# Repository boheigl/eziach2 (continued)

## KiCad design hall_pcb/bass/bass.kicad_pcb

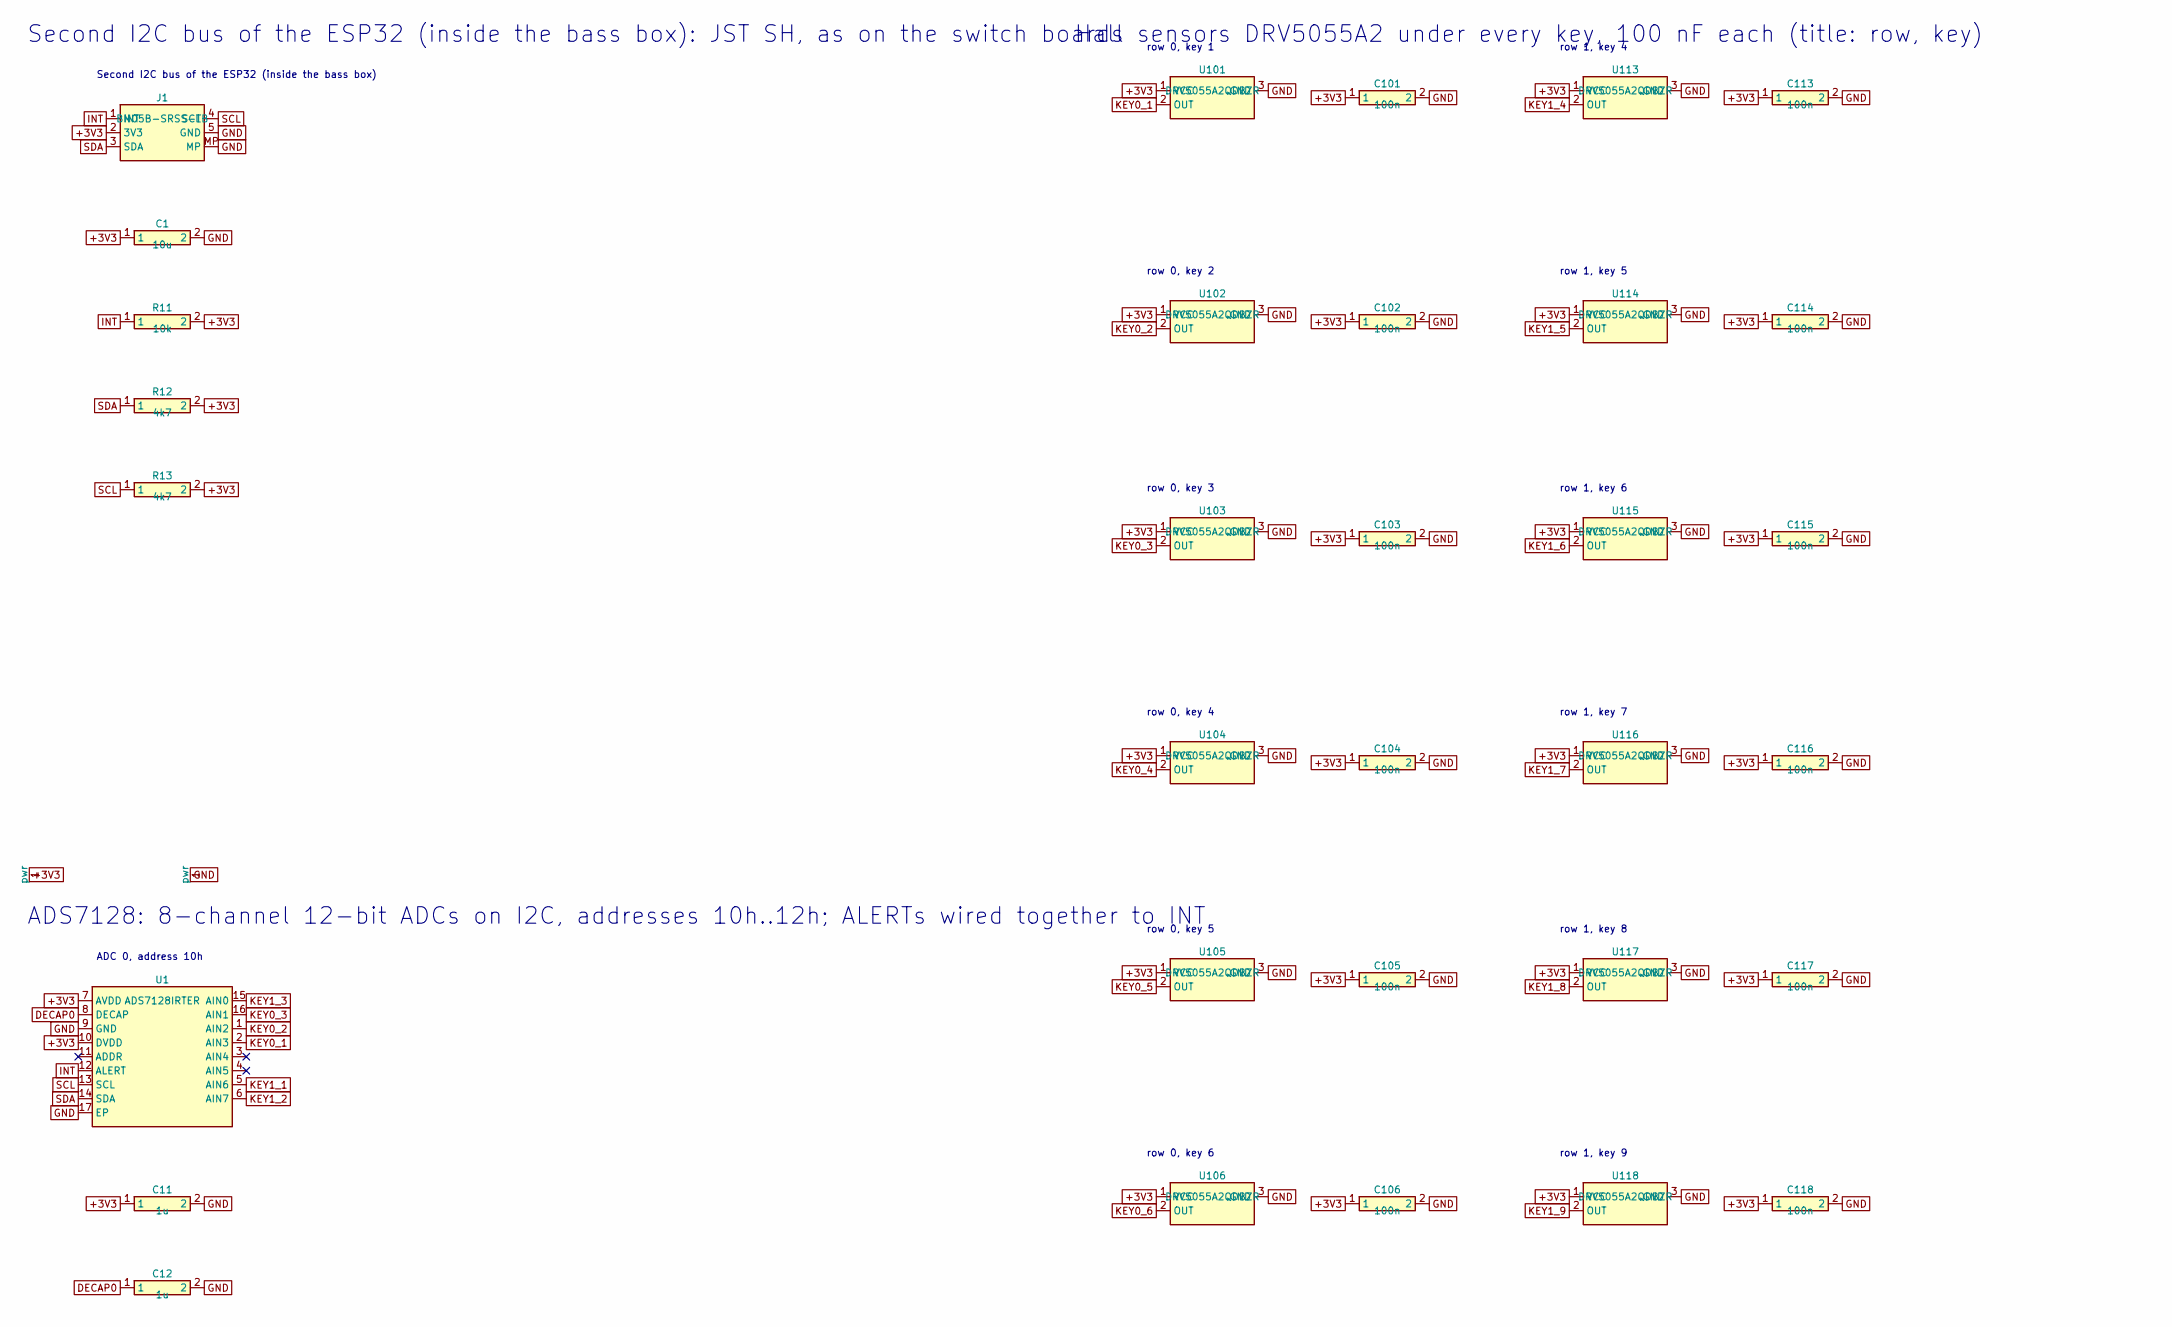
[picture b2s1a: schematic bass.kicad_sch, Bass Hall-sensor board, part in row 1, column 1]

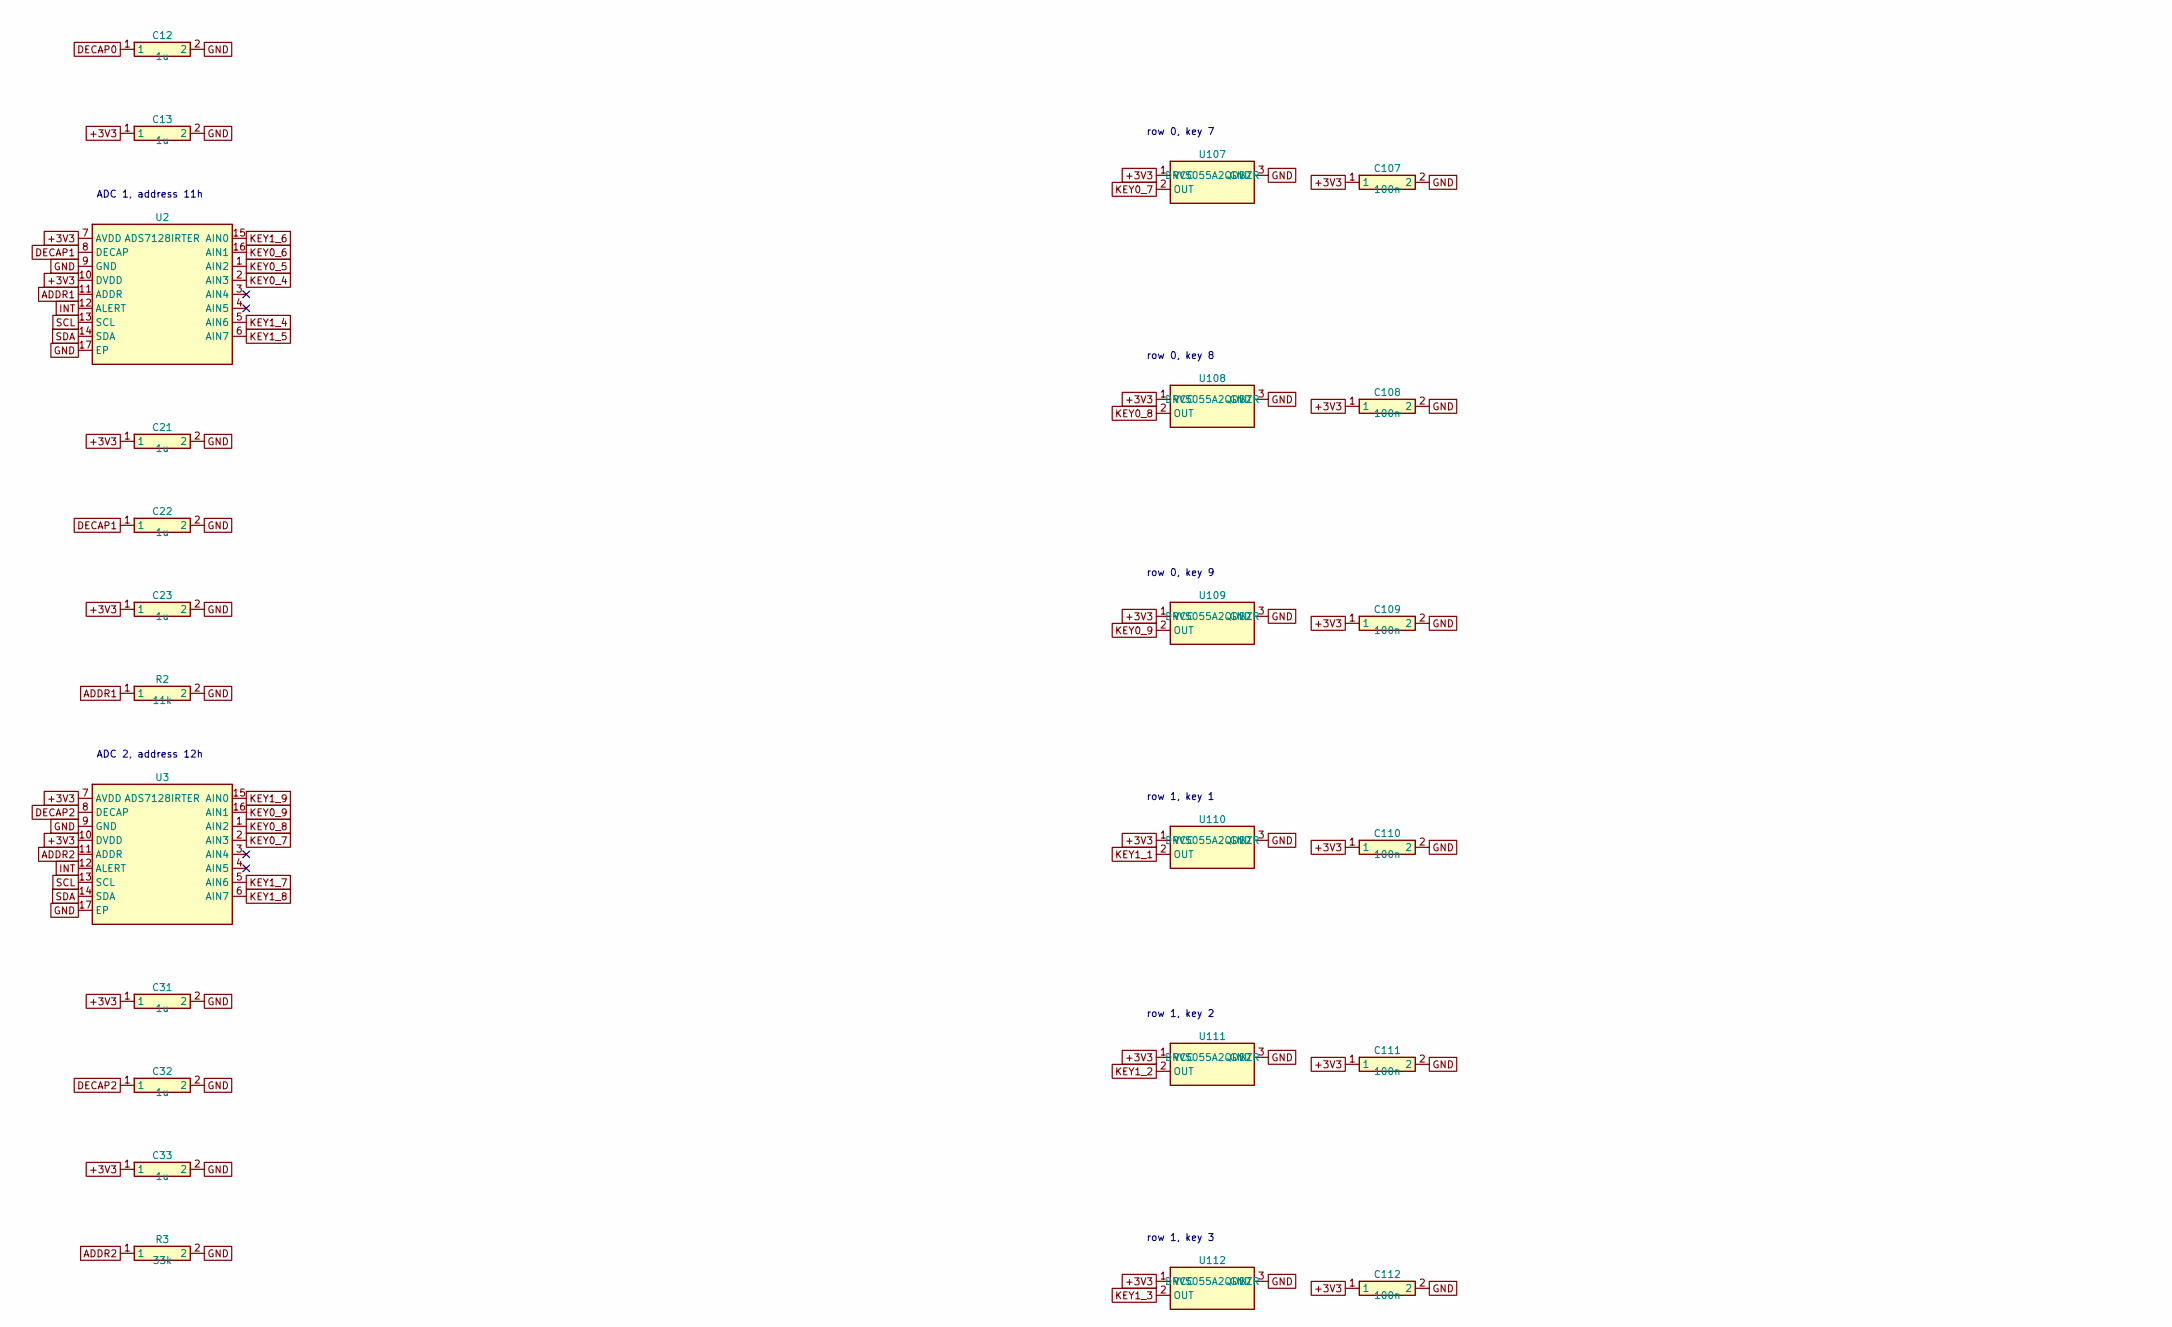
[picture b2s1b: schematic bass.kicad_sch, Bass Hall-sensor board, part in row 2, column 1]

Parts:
C1: 10u; C_0805_2012Metric; LCSC C15850
C11, C12, C13, C21, C22, C23, C31, C32, C33: 1u; C_0402_1005Metric; LCSC C52923
C101, C102, C103, C104, C105, C106, C107, C108, C109, C110, C111, C112, C113, C114, C115, C116, C117, C118: 100n; C_0402_1005Metric; LCSC C1525
J1: BM05B-SRSS-TB; JST_SH_BM05B-SRSS-TB_1x05-1MP_P1.00mm_Vertical; LCSC C160391
R2: 11k; R_0402_1005Metric; LCSC C25749
R3: 33k; R_0402_1005Metric; LCSC C25779
R11: 10k; R_0402_1005Metric; LCSC C25744
R12, R13: 4k7; R_0402_1005Metric; LCSC C25900
U1, U2, U3: ADS7128IRTER; WQFN-16-1EP_3x3mm_P0.5mm_EP1.68x1.68mm; LCSC C2867992
U101, U102, U103, U104, U105, U106, U107, U108, U109, U110, U111, U112, U113, U114, U115, U116, U117, U118: DRV5055A2QDBZR; SOT-23; LCSC C266131

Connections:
+3V3: C1.1, C11.1, C13.1, C21.1, C23.1, C31.1, C33.1, C101.1, C102.1, C103.1, C104.1, C105.1, C106.1, C107.1, C108.1, C109.1, C110.1, C111.1, C112.1, C113.1, C114.1, C115.1, C116.1, C117.1, C118.1, J1.2 (3V3), R11.2, R12.2, R13.2, U1.7 (AVDD), U1.10 (DVDD), U2.7 (AVDD), U2.10 (DVDD), U3.7 (AVDD), U3.10 (DVDD), U101.1 (VCC), U102.1 (VCC), U103.1 (VCC), U104.1 (VCC), U105.1 (VCC), U106.1 (VCC), U107.1 (VCC), U108.1 (VCC), U109.1 (VCC), U110.1 (VCC), U111.1 (VCC), U112.1 (VCC), U113.1 (VCC), U114.1 (VCC), U115.1 (VCC), U116.1 (VCC), U117.1 (VCC), U118.1 (VCC)
ADDR1: R2.1, U2.11 (ADDR)
ADDR2: R3.1, U3.11 (ADDR)
DECAP0: C12.1, U1.8 (DECAP)
DECAP1: C22.1, U2.8 (DECAP)
DECAP2: C32.1, U3.8 (DECAP)
GND: C1.2, C11.2, C12.2, C13.2, C21.2, C22.2, C23.2, C31.2, C32.2, C33.2, C101.2, C102.2, C103.2, C104.2, C105.2, C106.2, C107.2, C108.2, C109.2, C110.2, C111.2, C112.2, C113.2, C114.2, C115.2, C116.2, C117.2, C118.2, J1.5 (GND), J1.MP, R2.2, R3.2, U1.9 (GND), U1.17 (EP), U2.9 (GND), U2.17 (EP), U3.9 (GND), U3.17 (EP), U101.3 (GND), U102.3 (GND), U103.3 (GND), U104.3 (GND), U105.3 (GND), U106.3 (GND), U107.3 (GND), U108.3 (GND), U109.3 (GND), U110.3 (GND), U111.3 (GND), U112.3 (GND), U113.3 (GND), U114.3 (GND), U115.3 (GND), U116.3 (GND), U117.3 (GND), U118.3 (GND)
INT: J1.1 (INT), R11.1, U1.12 (ALERT), U2.12 (ALERT), U3.12 (ALERT)
KEY0_1: U1.2 (AIN3), U101.2 (OUT)
KEY0_2: U1.1 (AIN2), U102.2 (OUT)
KEY0_3: U1.16 (AIN1), U103.2 (OUT)
KEY0_4: U2.2 (AIN3), U104.2 (OUT)
KEY0_5: U2.1 (AIN2), U105.2 (OUT)
KEY0_6: U2.16 (AIN1), U106.2 (OUT)
KEY0_7: U3.2 (AIN3), U107.2 (OUT)
KEY0_8: U3.1 (AIN2), U108.2 (OUT)
KEY0_9: U3.16 (AIN1), U109.2 (OUT)
KEY1_1: U1.5 (AIN6), U110.2 (OUT)
KEY1_2: U1.6 (AIN7), U111.2 (OUT)
KEY1_3: U1.15 (AIN0), U112.2 (OUT)
KEY1_4: U2.5 (AIN6), U113.2 (OUT)
KEY1_5: U2.6 (AIN7), U114.2 (OUT)
KEY1_6: U2.15 (AIN0), U115.2 (OUT)
KEY1_7: U3.5 (AIN6), U116.2 (OUT)
KEY1_8: U3.6 (AIN7), U117.2 (OUT)
KEY1_9: U3.15 (AIN0), U118.2 (OUT)
SCL: J1.4 (SCL), R13.1, U1.13 (SCL), U2.13 (SCL), U3.13 (SCL)
SDA: J1.3 (SDA), R12.1, U1.14 (SDA), U2.14 (SDA), U3.14 (SDA)

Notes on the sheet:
Second I2C bus of the ESP32 (inside the bass box): JST SH, as on the switch boards
Second I2C bus of the ESP32 (inside the bass box)
ADS7128: 8-channel 12-bit ADCs on I2C, addresses 10h..12h; ALERTs wired together to INT
ADC 0, address 10h
ADC 1, address 11h
ADC 2, address 12h
Hall sensors DRV5055A2 under every key, 100 nF each (title: row, key)
row 0, key 1
row 0, key 2
row 0, key 3
row 0, key 4
row 0, key 5
row 0, key 6
row 0, key 7
row 0, key 8
row 0, key 9
row 1, key 1
row 1, key 2
row 1, key 3
row 1, key 4
row 1, key 5
row 1, key 6
row 1, key 7
row 1, key 8
row 1, key 9

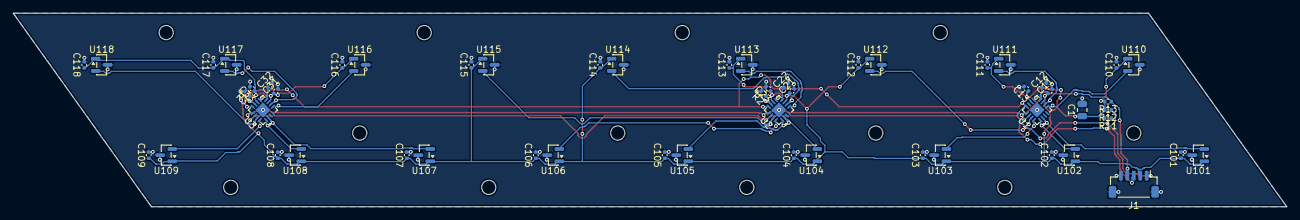
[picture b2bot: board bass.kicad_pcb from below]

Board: 2 copper layers, 197.4 x 30.0 mm, 55 parts (55 on the bottom side), 28 nets.

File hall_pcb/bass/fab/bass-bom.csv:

"Comment","Designator","Footprint","LCSC","Quantity"
"10u","C1","Capacitor_SMD:C_0805_2012Metric","C15850","1"
"100n","C101,C102,C103,C104,C105,C106,C107,C108,C109,C110,C111,C112,C113,C114,C115,C116,C117,C118","Capacitor_SMD:C_0402_1005Metric","C1525","18"
"1u","C11,C12,C13,C21,C22,C23,C31,C32,C33","Capacitor_SMD:C_0402_1005Metric","C52923","9"
"BM05B-SRSS-TB","J1","Connector_JST:JST_SH_BM05B-SRSS-TB_1x05-1MP_P1.00mm_Vertical","C160391","1"
"11k","R2","Resistor_SMD:R_0402_1005Metric","C25749","1"
"33k","R3","Resistor_SMD:R_0402_1005Metric","C25779","1"
"10k","R11","Resistor_SMD:R_0402_1005Metric","C25744","1"
"4k7","R12,R13","Resistor_SMD:R_0402_1005Metric","C25900","2"
"ADS7128IRTER","U1,U2,U3","Package_DFN_QFN:WQFN-16-1EP_3x3mm_P0.5mm_EP1.68x1.68mm","C2867992","3"
"DRV5055A2QDBZR","U101,U102,U103,U104,U105,U106,U107,U108,U109,U110,U111,U112,U113,U114,U115,U116,U117,U118","Package_TO_SOT_SMD:SOT-23","C266131","18"

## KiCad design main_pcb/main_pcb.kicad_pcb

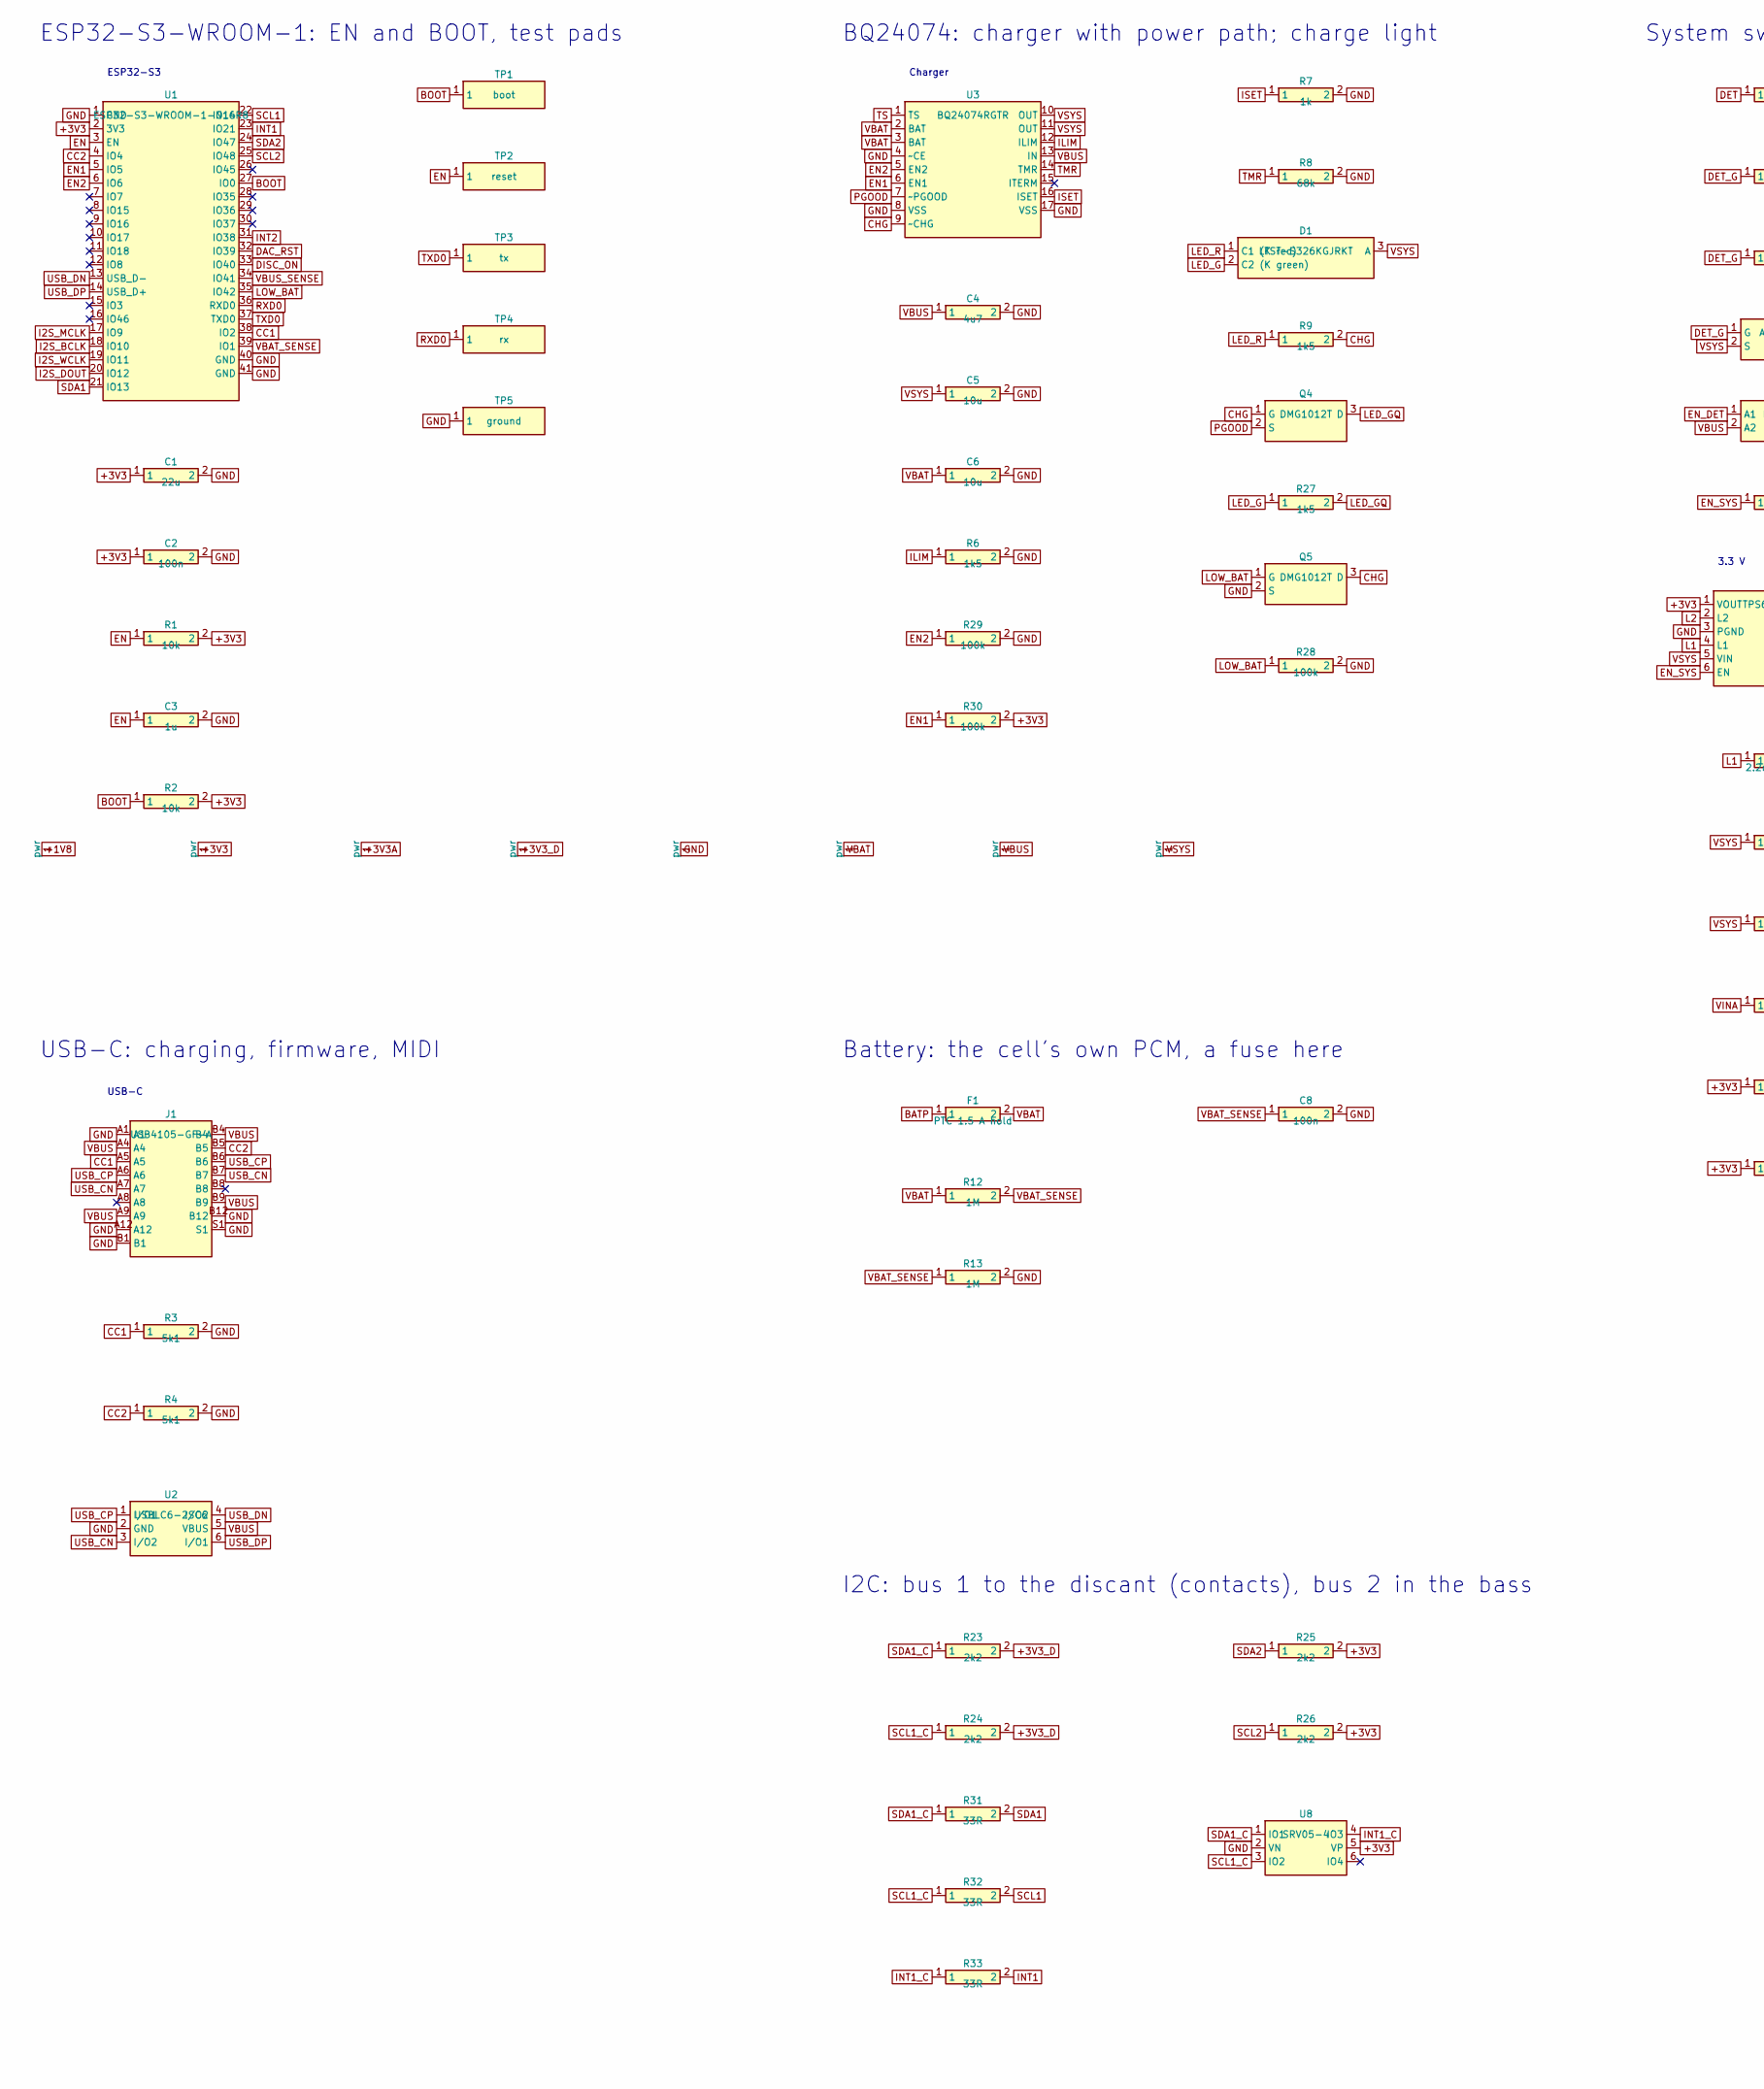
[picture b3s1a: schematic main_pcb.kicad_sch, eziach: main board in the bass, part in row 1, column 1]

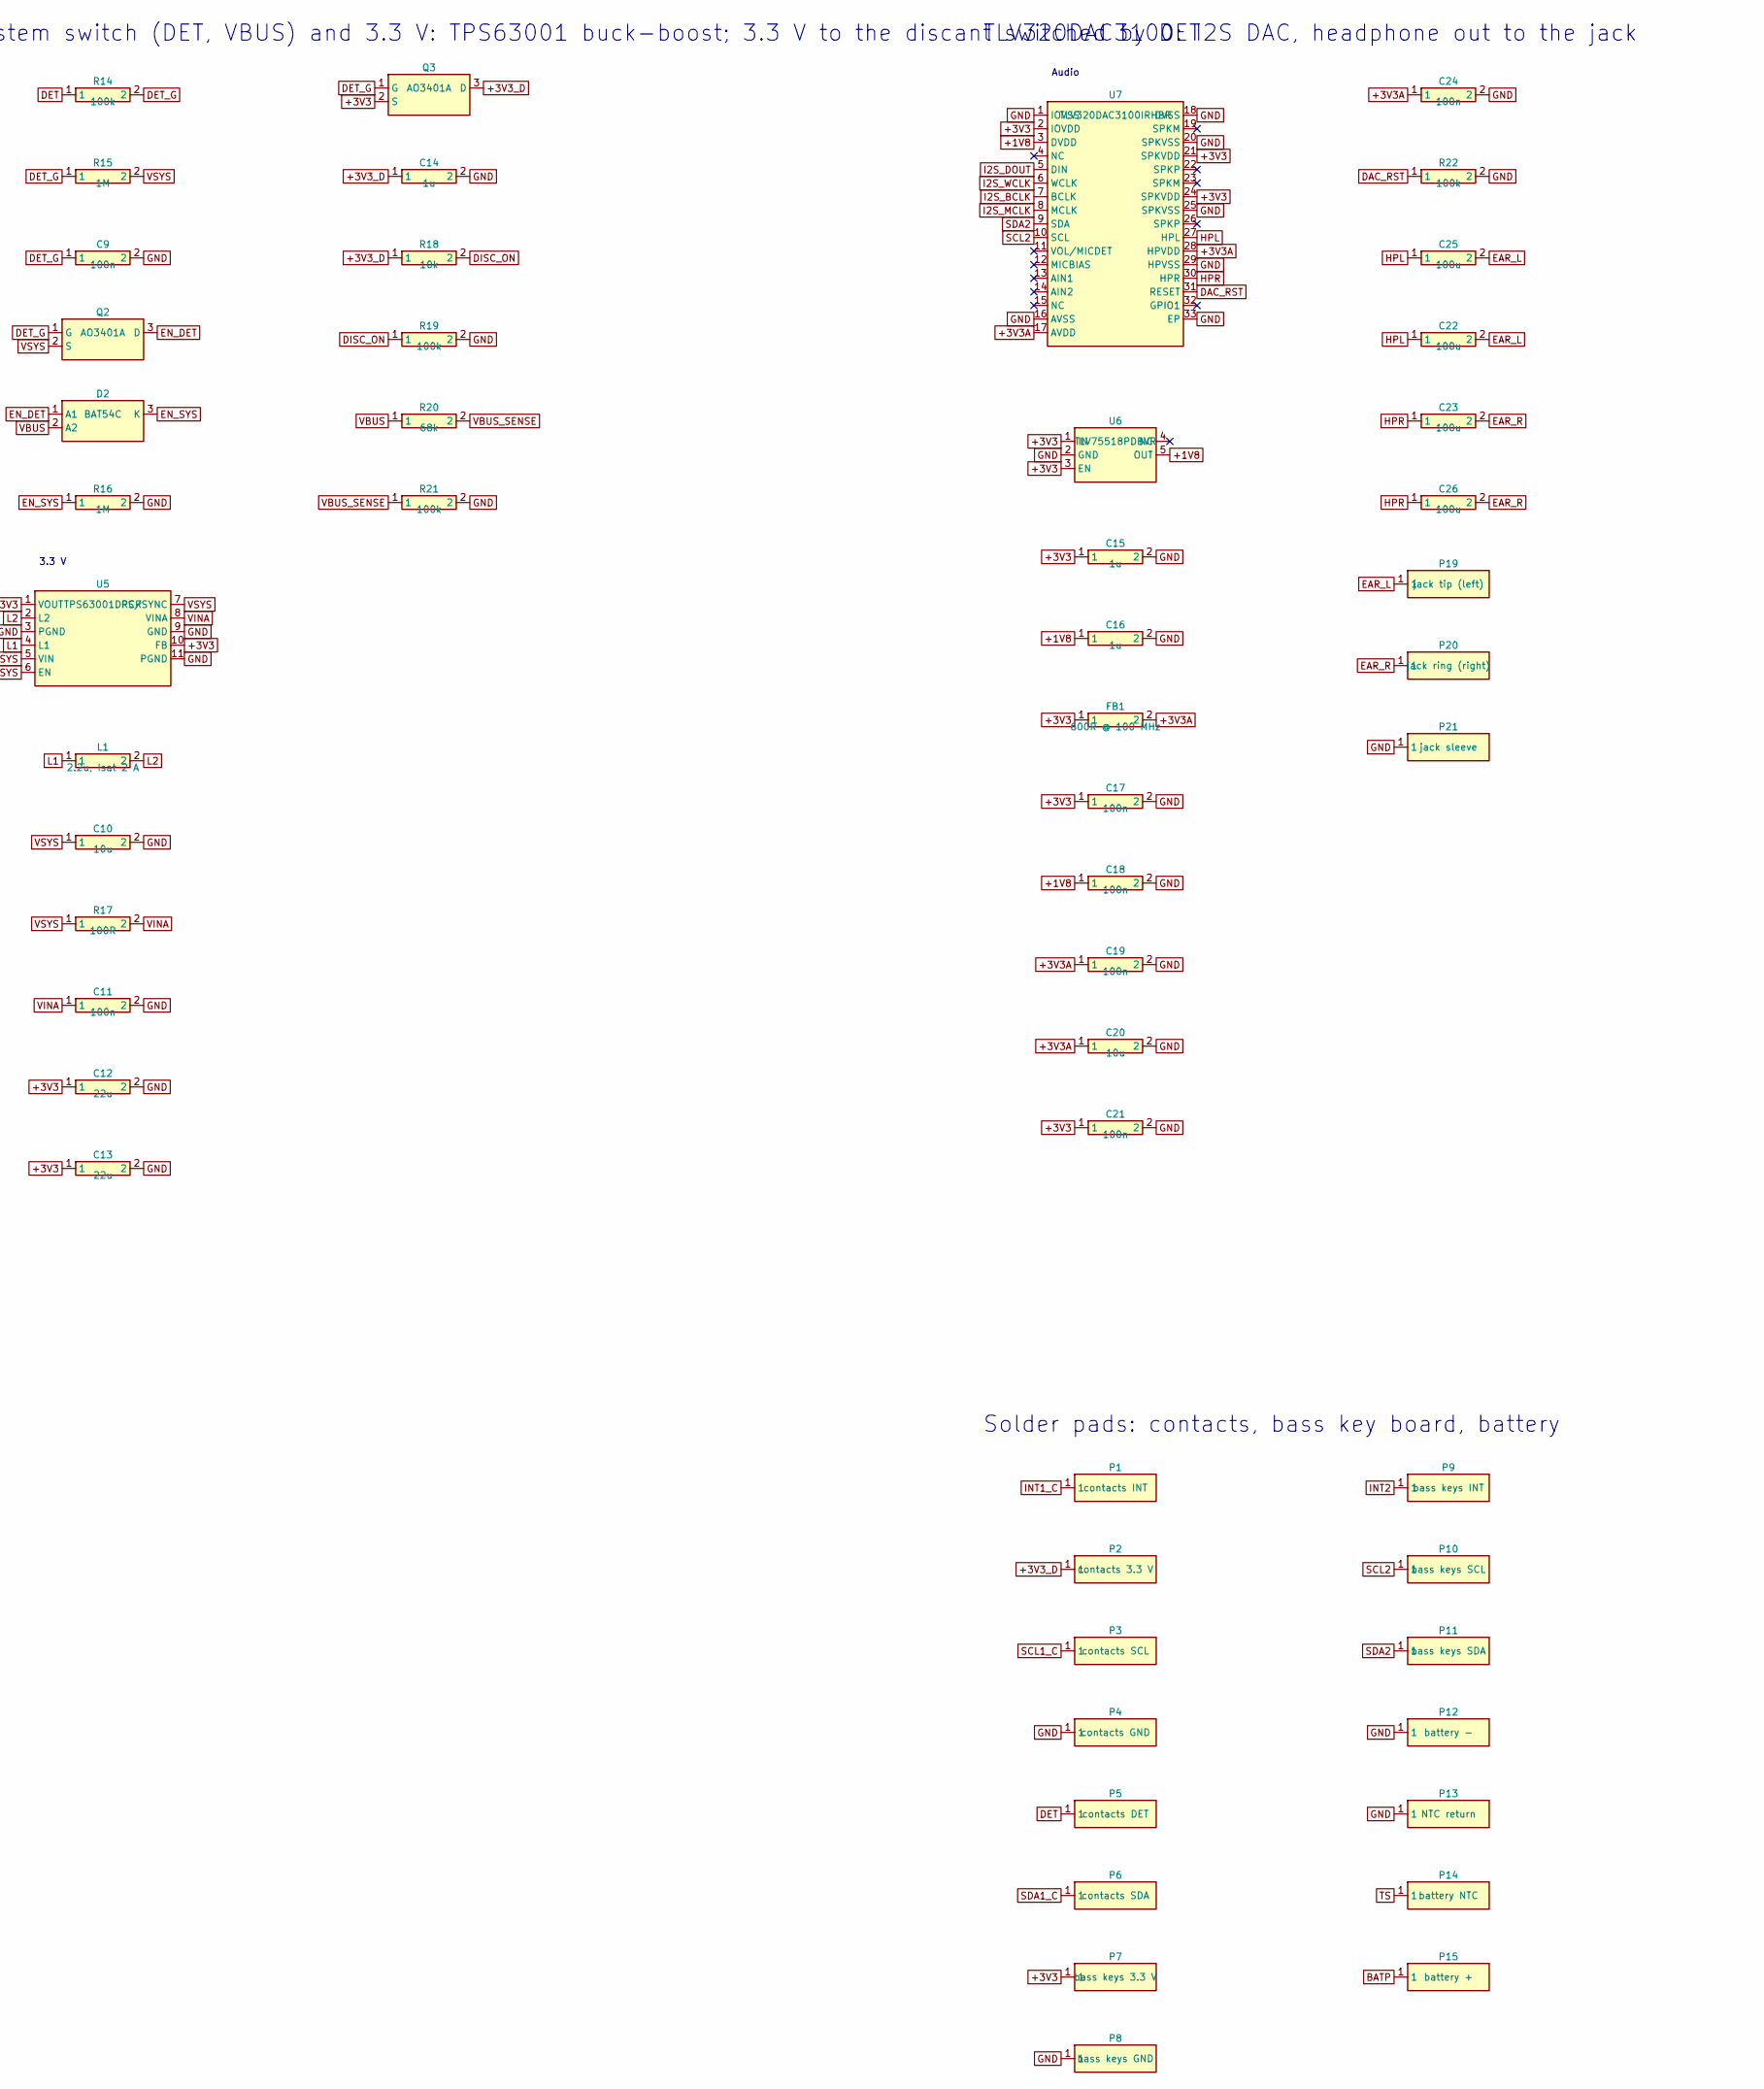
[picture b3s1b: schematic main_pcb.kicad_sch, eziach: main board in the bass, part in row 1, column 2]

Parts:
C1, C12, C13: 22u; C_0805_2012Metric; LCSC C45783
C2, C8, C9, C11, C17, C18, C19, C21, C24: 100n; C_0402_1005Metric; LCSC C1525
C3, C14, C15, C16: 1u; C_0402_1005Metric; LCSC C52923
C4: 4u7; C_0603_1608Metric; LCSC C19666
C5, C6: 10u; C_0603_1608Metric; LCSC C19702
C10: 10u; C_0805_2012Metric; LCSC C15850
C20: 10u; C_0402_1005Metric; LCSC C15525
C22, C23, C25, C26: 100u; C_0805_2012Metric; LCSC C141660
D1: LTST-S326KGJRKT; LED_LiteOn_LTST-S326; LCSC C125116
D2: BAT54C; SOT-23; LCSC C37704
F1: PTC 1.5 A hold; Fuse_1206_3216Metric; LCSC C20802
FB1: 600R @ 100 MHz; L_0402_1005Metric; LCSC C76884
J1: USB4105-GF-A; USB_C_Receptacle_GCT_USB4105-xx-A_16P_TopMnt_Horizontal; LCSC C3020560
L1: 2.2u, Isat 2 A; L_1008_2520Metric; LCSC C23894
P1: contacts INT; TestPoint_THTPad_D1.5mm_Drill0.7mm
P2: contacts 3.3 V; TestPoint_THTPad_D1.5mm_Drill0.7mm
P3: contacts SCL; TestPoint_THTPad_D1.5mm_Drill0.7mm
P4: contacts GND; TestPoint_THTPad_D1.5mm_Drill0.7mm
P5: contacts DET; TestPoint_THTPad_D1.5mm_Drill0.7mm
P6: contacts SDA; TestPoint_THTPad_D1.5mm_Drill0.7mm
P7: bass keys 3.3 V; TestPoint_THTPad_D1.5mm_Drill0.7mm
P8: bass keys GND; TestPoint_THTPad_D1.5mm_Drill0.7mm
P9: bass keys INT; TestPoint_THTPad_D1.5mm_Drill0.7mm
P10: bass keys SCL; TestPoint_THTPad_D1.5mm_Drill0.7mm
P11: bass keys SDA; TestPoint_THTPad_D1.5mm_Drill0.7mm
P12: battery -; TestPoint_THTPad_D1.5mm_Drill0.7mm
P13: NTC return; TestPoint_THTPad_D1.5mm_Drill0.7mm
P14: battery NTC; TestPoint_THTPad_D1.5mm_Drill0.7mm
P15: battery +; TestPoint_THTPad_D1.5mm_Drill0.7mm
P19: jack tip (left); TestPoint_Pad_1.0x1.0mm
P20: jack ring (right); TestPoint_Pad_1.0x1.0mm
P21: jack sleeve; TestPoint_Pad_1.0x1.0mm
Q2, Q3: AO3401A; SOT-23; LCSC C15127
Q4, Q5: DMG1012T; SOT-523; LCSC C20512
R1, R2, R18: 10k; R_0402_1005Metric; LCSC C25744
R3, R4: 5k1; R_0402_1005Metric; LCSC C25905
R6, R9, R27: 1k5; R_0402_1005Metric; LCSC C25867
R7: 1k; R_0402_1005Metric; LCSC C11702
R8, R20: 68k; R_0402_1005Metric; LCSC C36871
R12, R13, R15, R16: 1M; R_0402_1005Metric; LCSC C26083
R14, R19, R21, R22, R28, R29, R30: 100k; R_0402_1005Metric; LCSC C25741
R17: 100R; R_0402_1005Metric; LCSC C25076
R23, R24, R25, R26: 2k2; R_0402_1005Metric; LCSC C25879
R31, R32, R33: 33R; R_0402_1005Metric; LCSC C25105
TP1: boot; TestPoint_Pad_1.0x1.0mm
TP2: reset; TestPoint_Pad_1.0x1.0mm
TP3: tx; TestPoint_Pad_1.0x1.0mm
TP4: rx; TestPoint_Pad_1.0x1.0mm
TP5: ground; TestPoint_Pad_1.0x1.0mm
U1: ESP32-S3-WROOM-1-N16R8; ESP32-S3-WROOM-1; LCSC C2913202
U2: USBLC6-2SC6; SOT-23-6; LCSC C7519
U3: BQ24074RGTR; VQFN-16-1EP_3x3mm_P0.5mm_EP1.6x1.6mm; LCSC C54313
U5: TPS63001DRCR; Texas_DRC0010J; LCSC C28060
U6: TLV75518PDBVR; SOT-23-5; LCSC C2877863
U7: TLV320DAC3100IRHBR; VQFN-32-1EP_5x5mm_P0.5mm_EP3.1x3.1mm; LCSC C179677
U8: SRV05-4; SOT-23-6; LCSC C85364

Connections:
+1V8: C16.1, C18.1, U6.5 (OUT), U7.3 (DVDD)
+3V3: C1.1, C2.1, C12.1, C13.1, C15.1, C17.1, C21.1, FB1.1, P7.1, Q3.2 (S), R1.2, R2.2, R25.2, R26.2, R30.2, U1.2 (3V3), U5.1 (VOUT), U5.10 (FB), U6.1 (IN), U6.3 (EN), U7.2 (IOVDD), U7.21 (SPKVDD), U7.24 (SPKVDD), U8.5 (VP)
+3V3A: C19.1, C20.1, C24.1, FB1.2, U7.17 (AVDD), U7.28 (HPVDD)
+3V3_D: C14.1, P2.1, Q3.3 (D), R18.1, R23.2, R24.2
BATP: F1.1, P15.1
BOOT: R2.1, TP1.1, U1.27 (IO0)
CC1: J1.A5, R3.1, U1.38 (IO2)
CC2: J1.B5, R4.1, U1.4 (IO4)
CHG: Q4.1 (G), Q5.3 (D), R9.2, U3.9 (~CHG)
DAC_RST: R22.1, U1.32 (IO39), U7.31 (RESET)
DET: P5.1, R14.1
DET_G: C9.1, Q2.1 (G), Q3.1 (G), R14.2, R15.1
DISC_ON: R18.2, R19.1, U1.33 (IO40)
EAR_L: C22.2, C25.2, P19.1
EAR_R: C23.2, C26.2, P20.1
EN: C3.1, R1.1, TP2.1, U1.3 (EN)
EN1: R30.1, U1.5 (IO5), U3.6 (EN1)
EN2: R29.1, U1.6 (IO6), U3.5 (EN2)
EN_DET: D2.1 (A1), Q2.3 (D)
EN_SYS: D2.3 (K), R16.1, U5.6 (EN)
GND: C1.2, C2.2, C3.2, C4.2, C5.2, C6.2, C8.2, C9.2, C10.2, C11.2, C12.2, C13.2, C14.2, C15.2, C16.2, C17.2, C18.2, C19.2, C20.2, C21.2, C24.2, J1.A1, J1.A12, J1.B1, J1.B12, J1.S1, P4.1, P8.1, P12.1, P13.1, P21.1, Q5.2 (S), R3.2, R4.2, R6.2, R7.2, R8.2, R13.2, R16.2, R19.2, R21.2, R22.2, R28.2, R29.2, TP5.1, U1.1 (GND), U1.40 (GND), U1.41 (GND), U2.2 (GND), U3.4 (~CE), U3.8 (VSS), U3.17 (VSS), U5.3 (PGND), U5.9 (GND), U5.11 (PGND), U6.2 (GND), U7.1 (IOVSS), U7.16 (AVSS), U7.18 (DVSS), U7.20 (SPKVSS), U7.25 (SPKVSS), U7.29 (HPVSS), U7.33 (EP), U8.2 (VN)
HPL: C22.1, C25.1, U7.27 (HPL)
HPR: C23.1, C26.1, U7.30 (HPR)
I2S_BCLK: U1.18 (IO10), U7.7 (BCLK)
I2S_DOUT: U1.20 (IO12), U7.5 (DIN)
I2S_MCLK: U1.17 (IO9), U7.8 (MCLK)
I2S_WCLK: U1.19 (IO11), U7.6 (WCLK)
ILIM: R6.1, U3.12 (ILIM)
INT1: R33.2, U1.23 (IO21)
INT1_C: P1.1, R33.1, U8.4 (IO3)
INT2: P9.1, U1.31 (IO38)
ISET: R7.1, U3.16 (ISET)
L1: L1.1, U5.4 (L1)
L2: L1.2, U5.2 (L2)
LED_G: D1.2 (C2 (K green)), R27.1
LED_GQ: Q4.3 (D), R27.2
LED_R: D1.1 (C1 (K red)), R9.1
LOW_BAT: Q5.1 (G), R28.1, U1.35 (IO42)
PGOOD: Q4.2 (S), U3.7 (~PGOOD)
RXD0: TP4.1, U1.36 (RXD0)
SCL1: R32.2, U1.22 (IO14)
SCL1_C: P3.1, R24.1, R32.1, U8.3 (IO2)
SCL2: P10.1, R26.1, U1.25 (IO48), U7.10 (SCL)
SDA1: R31.2, U1.21 (IO13)
SDA1_C: P6.1, R23.1, R31.1, U8.1 (IO1)
SDA2: P11.1, R25.1, U1.24 (IO47), U7.9 (SDA)
TMR: R8.1, U3.14 (TMR)
TS: P14.1, U3.1 (TS)
TXD0: TP3.1, U1.37 (TXD0)
USB_CN: J1.A7, J1.B7, U2.3 (I/O2)
USB_CP: J1.A6, J1.B6, U2.1 (I/O1)
USB_DN: U1.13 (USB_D-), U2.4 (I/O2)
USB_DP: U1.14 (USB_D+), U2.6 (I/O1)
VBAT: C6.1, F1.2, R12.1, U3.2 (BAT), U3.3 (BAT)
VBAT_SENSE: C8.1, R12.2, R13.1, U1.39 (IO1)
VBUS: C4.1, D2.2 (A2), J1.A4, J1.A9, J1.B4, J1.B9, R20.1, U2.5 (VBUS), U3.13 (IN)
VBUS_SENSE: R20.2, R21.1, U1.34 (IO41)
VINA: C11.1, R17.2, U5.8 (VINA)
VSYS: C5.1, C10.1, D1.3 (A), Q2.2 (S), R15.2, R17.1, U3.10 (OUT), U3.11 (OUT), U5.5 (VIN), U5.7 (PS/SYNC)

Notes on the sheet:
ESP32-S3-WROOM-1: EN and BOOT, test pads
ESP32-S3
USB-C: charging, firmware, MIDI
USB-C
BQ24074: charger with power path; charge light
Charger
Battery: the cell's own PCM, a fuse here
System switch (DET, VBUS) and 3.3 V: TPS63001 buck-boost; 3.3 V to the discant switched by DET
3.3 V
TLV320DAC3100: I2S DAC, headphone out to the jack
Audio
I2C: bus 1 to the discant (contacts), bus 2 in the bass
Solder pads: contacts, bass key board, battery

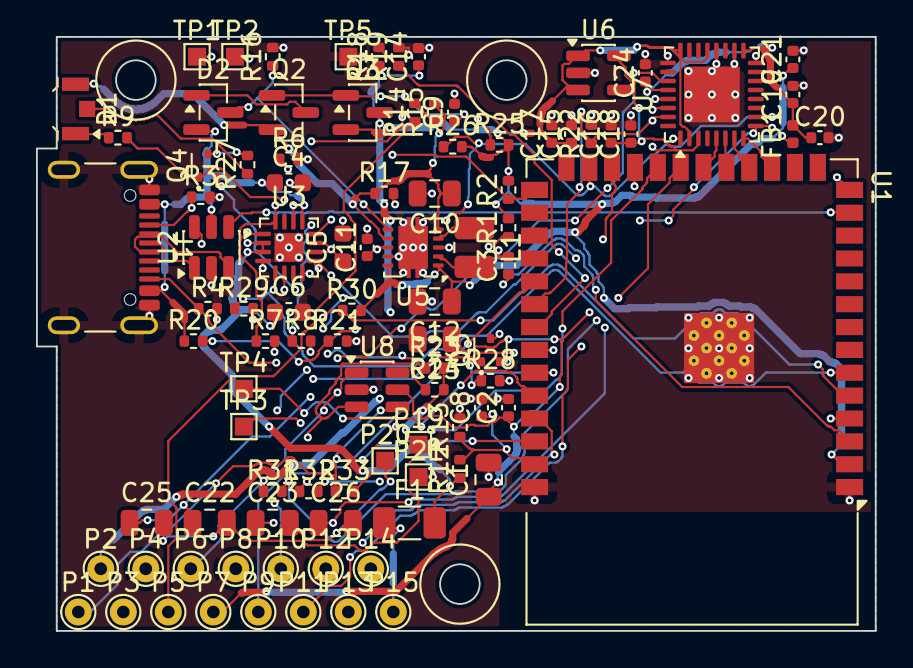
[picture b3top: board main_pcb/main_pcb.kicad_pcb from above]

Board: 4 copper layers, 46.6 x 33.0 mm, 95 parts (0 on the bottom side), 59 nets.

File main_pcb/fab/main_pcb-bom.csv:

"Comment","Designator","Footprint","LCSC","Quantity"
"4u7","C4","Capacitor_SMD:C_0603_1608Metric","C19666","1"
"10u","C10","Capacitor_SMD:C_0805_2012Metric","C15850","1"
"10u","C20","Capacitor_SMD:C_0402_1005Metric","C15525","1"
"22u","C1,C12,C13","Capacitor_SMD:C_0805_2012Metric","C45783","3"
"100n","C2,C8,C9,C11,C17-C19,C21,C24","Capacitor_SMD:C_0402_1005Metric","C1525","9"
"100u","C22,C23,C25,C26","Capacitor_SMD:C_0805_2012Metric","C141660","4"
"1u","C3,C14-C16","Capacitor_SMD:C_0402_1005Metric","C52923","4"
"10u","C5,C6","Capacitor_SMD:C_0603_1608Metric","C19702","2"
"LTST-S326KGJRKT","D1","LED_SMD:LED_LiteOn_LTST-S326","C125116","1"
"BAT54C","D2","Package_TO_SOT_SMD:SOT-23","C37704","1"
"PTC 1.5 A hold","F1","Fuse:Fuse_1206_3216Metric","C20802","1"
"600R @ 100 MHz","FB1","Inductor_SMD:L_0402_1005Metric","C76884","1"
"USB4105-GF-A","J1","Connector_USB:USB_C_Receptacle_GCT_USB4105-xx-A_16P_TopMnt_Horizontal","C3020560","1"
"2.2u, Isat 2 A","L1","Inductor_SMD:L_1008_2520Metric","C23894","1"
"AO3401A","Q2,Q3","Package_TO_SOT_SMD:SOT-23","C15127","2"
"DMG1012T","Q4,Q5","Package_TO_SOT_SMD:SOT-523","C20512","2"
"1k","R7","Resistor_SMD:R_0402_1005Metric","C11702","1"
"100R","R17","Resistor_SMD:R_0402_1005Metric","C25076","1"
"10k","R1,R2,R18","Resistor_SMD:R_0402_1005Metric","C25744","3"
"1M","R12,R13,R15,R16","Resistor_SMD:R_0402_1005Metric","C26083","4"
"100k","R14,R19,R21,R22,R28-R30","Resistor_SMD:R_0402_1005Metric","C25741","7"
"2k2","R23-R26","Resistor_SMD:R_0402_1005Metric","C25879","4"
"5k1","R3,R4","Resistor_SMD:R_0402_1005Metric","C25905","2"
"33R","R31-R33","Resistor_SMD:R_0402_1005Metric","C25105","3"
"1k5","R6,R9,R27","Resistor_SMD:R_0402_1005Metric","C25867","3"
"68k","R8,R20","Resistor_SMD:R_0402_1005Metric","C36871","2"
"ESP32-S3-WROOM-1-N16R8","U1","RF_Module:ESP32-S3-WROOM-1","C2913202","1"
"USBLC6-2SC6","U2","Package_TO_SOT_SMD:SOT-23-6","C7519","1"
"BQ24074RGTR","U3","Package_DFN_QFN:VQFN-16-1EP_3x3mm_P0.5mm_EP1.6x1.6mm","C54313","1"
"TPS63001DRCR","U5","Package_SON:Texas_DRC0010J","C28060","1"
"TLV75518PDBVR","U6","Package_TO_SOT_SMD:SOT-23-5","C2877863","1"
"TLV320DAC3100IRHBR","U7","Package_DFN_QFN:VQFN-32-1EP_5x5mm_P0.5mm_EP3.1x3.1mm","C179677","1"
"SRV05-4","U8","Package_TO_SOT_SMD:SOT-23-6","C85364","1"
